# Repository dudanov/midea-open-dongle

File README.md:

# midea-open-dongle

# This project is no longer developing. Please use the [iot-uni-dongle](https://github.com/dudanov/iot-uni-dongle) project.

An open project for a stick for air conditioners controlled by the Midea UART protocol.

A far from complete list of supported brands:
1. [Midea](https://www.midea.com/)
2. [Electrolux](https://www.electrolux.ru/)
3. [Qlima](https://www.qlima.com/)
4. [Artel](https://www.artelgroup.com/)
5. [Carrier](https://www.carrier.com/)
6. [Comfee](http://www.comfee-russia.ru/)
7. [Inventor](https://www.inventorairconditioner.com/)

Board dimensions: 49x20mm, antennas: + 7mm, USB connector: + 15mm, overall: 71x20mm.

Description of files:
* [schematic.pdf](schematic.pdf) - schematic diagram
* [gerber.zip](gerber.zip) - files for making a printed circuit board
* [bom.csv](bom.csv) - bill of materials
* [position.csv](position.csv) - CPL/POS file

The last 3 files can be used to order a stick from the [JLCPCB](https://jlcpcb.com) factory. All that remains is to solder the radio module and the USB connector yourself.

## Imitation of IR remote control commands

Due to the fact that not all capabilities are implemented in the UART protocol (for example, indication control and `FollowMe` feature), it is possible to simulate IR commands by supplying a demodulated signal to pin `GPIO13`.
To do this, connect the `IR_TSOP` pad located on the back of the stick and the output of the IR demodulator on the display board.
The pictures below show an example for a `TSOP1738` IR receiver.

## Frequently asked Questions:
> How can I tell if my air conditioner is supported or not?

*None 100% answer to the question. But there is a high probability of support if your air conditioner has a USB connector, a regular place for a stick, UART is used.*

> What firmware would you recommend?

*Initially, the stick was developed for [ESPHome](https://esphome.io) and [Home Assistant](https://www.home-assistant.io), but it is possible to write your own firmware for your tasks and needs if you have the appropriate skills.*

> Is it possible to purchase a ready-made stick?

*Yes, you can write me to my [Telegram](https://t.me/dudanov) or [e-mail](mailto:sergey.dudanov@gmail.com).*

If this project was useful to you, you can [buy me](https://paypal.me/dudan0v) a Cup of coffee :)

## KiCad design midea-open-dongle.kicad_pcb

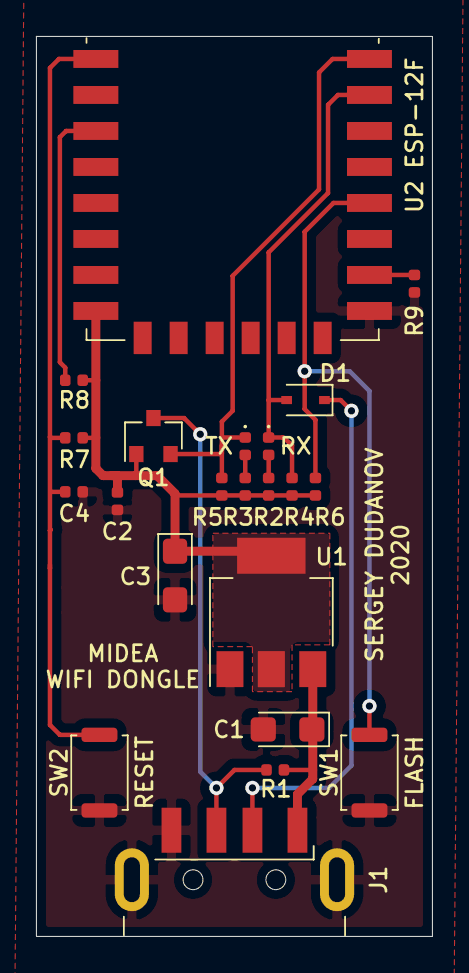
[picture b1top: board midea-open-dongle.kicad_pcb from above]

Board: 2 copper layers, 22.0 x 50.0 mm, 22 parts (0 on the bottom side), 13 nets.

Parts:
C1: 10uF; CP_EIA-3216-10_Kemet-I
C2: 100nF; C_0402_1005Metric
C3: 47uF; CP_EIA-3216-10_Kemet-I
C4: 470pF; C_0402_1005Metric
D1: 1N5819; D_SOD-323
D2: RX; LED_0402_1005Metric
D3: TX; LED_0402_1005Metric
J1: USB Type A; USB_A_CNCTech_1001-011-01101_Horizontal
Q1: BSS138; SOT-23
R1, R4, R5, R6, R7, R8, R9: 10K; R_0402_1005Metric
R2, R3: 2.2K; R_0402_1005Metric
SW1: FLASH; SW_Push_SPST_NO_Alps_SKRK
SW2: RESET; SW_Push_SPST_NO_Alps_SKRK
U1: AMS1117-3.3; SOT-223-3_TabPin2
U2: ESP-12F; ESP-12E

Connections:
+3V3: C2.2, C3.1, Q1.1, R2.1, R3.1, R4.1, R5.1, R6.2, R7.2, R8.2, U1.2, U2.8
+5V: C1.1, J1.1, R1.1, U1.3
/EN: R8.1, U2.3
/GPIO0: R6.1, SW1.2, U2.18
/GPIO15: R9.1, U2.16
/RESET: C4.1, R7.1, SW2.2, U2.1
/RXD: D1.2, D2.1, R4.2, U2.21
/RXD_AC: J1.3, Q1.3, R1.2
/TXD: D3.1, Q1.2, R5.2, U2.22
/TXD_AC: D1.1, J1.2
GND: C1.2, C2.1, C3.2, C4.2, J1.4, J1.5, R9.2, SW1.1, SW2.1, U1.1, U2.15
unnamed: D2.2, R2.2
unnamed: D3.2, R3.2

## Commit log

2021-06-14 Add BOM and POS files
